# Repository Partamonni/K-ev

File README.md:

# K-ev
K-ev electric motorcycle repo

New, rewritten fork is available at https://github.com/Partamonni/K-ev3

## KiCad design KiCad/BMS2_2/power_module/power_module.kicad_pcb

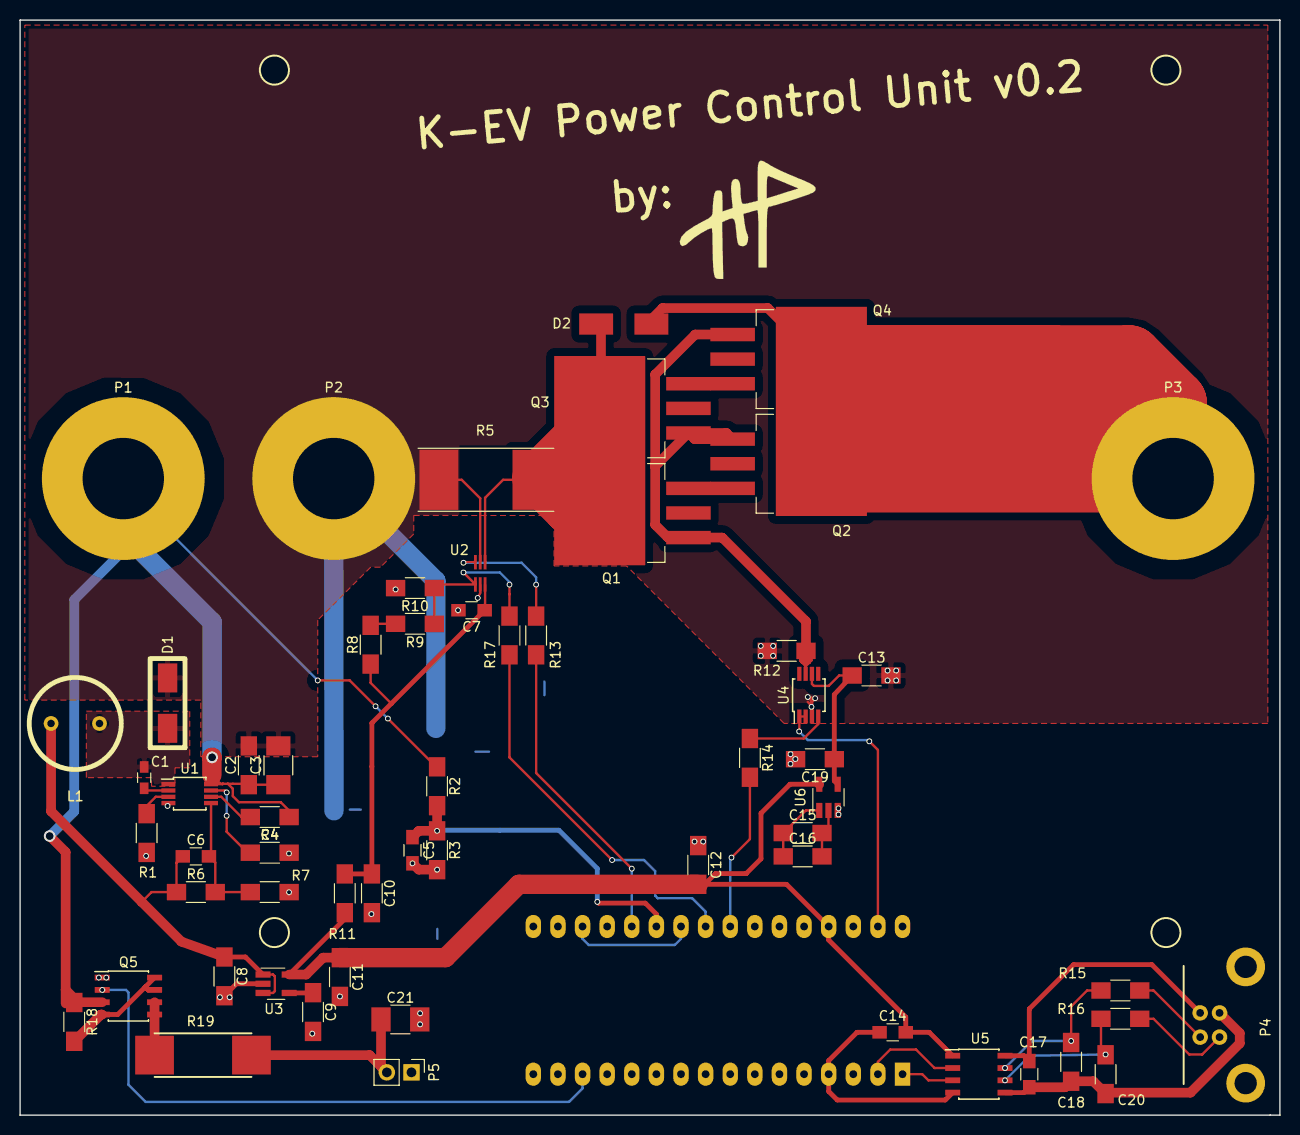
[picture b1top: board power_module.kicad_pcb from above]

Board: 2 copper layers, 130.0 x 113.0 mm, 60 parts (1 on the bottom side), 42 nets.

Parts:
C1: 0.022uF; R_0603_HandSoldering
C2: 0.1uF; R_1206_HandSoldering
C3: 1uF; R_1210_HandSoldering
C4, C8, C10, C11, C12, C13, C15, C16, C18, C20: 1uF; R_1206_HandSoldering
C5, C6, C7, C14, C17: 0.1uF; R_0805_HandSoldering
C9: 1nF; R_1206_HandSoldering
C19: 10uF; R_1206_HandSoldering
C21: 1uF; C_1210_HandSoldering
D1: RFN1L6S; ROHM_RFN1L6S_HAND_SOLDER
D2: TVS; DO-214AA
IC1: ArduinoNano; DIP-32_W15.24mm_Socket_LongPads_Arduino_Nano
L1: 150uH; Bourns_RLB0914-151KL
P1: BATT +; MountingHole_8.4mm_M8_Pad
P2: BATT -; MountingHole_8.4mm_M8_Pad
P3: 72V-; MountingHole_8.4mm_M8_Pad
P4: toRasPi; USB_B_JACK
P5: FAN; Pin_Header_Straight_1x02_Pitch2.54mm
Q1, Q2, Q3, Q4: CSD19535KTT; TO-263-3Lead
Q5: ZXMC10A816N8; SOIC-8_3.9x4.9mm_Pitch1.27mm
R1, R4: 220K; R_1206_HandSoldering
R2: 510K; R_1206_HandSoldering
R3: 27K; R_1206_HandSoldering
R5: 0.2mOhm; Bourns_CSS2H-3920_200uOhm_hand_solder
R6: 1.2K; R_1206_HandSoldering
R7, R13, R14, R17: 1K; R_1206_HandSoldering
R8, R9: 20K; R_1206_HandSoldering
R10, R18: 10K; R_1206_HandSoldering
R11, R15, R16: 100; R_1206_HandSoldering
R12: 100K; R_1206_HandSoldering
R19: 100; TE_SMW_3
U1: LM5009; MSOP-8_3x3mm_Pitch0.65mm
U2: INA214; SC-70-6_Handsoldering
U3: TC1185; SOT-23-5_HandSoldering
U4: LM5112; MSOP-8_3x3mm_Pitch0.65mm
U5: SI8422; SOIC-8_3.9x4.9mm_Pitch1.27mm
U6: MAX1683; SOT-23-5_HandSoldering

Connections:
+5V: C11.1, C12.2, C14.2, IC1.27, R11.2, U3.5, U5.1, U6.4
+5VA: C7.1, C10.1, R8.1, R11.1, U2.3
+10V: C13.1, C19.1, U4.6, U6.2
GND: C2.2, C3.2, C4.2, C5.2, C7.2, C8.2, C9.2, C10.2, C11.2, C12.1, C13.2, C19.2, C21.2, D1.2, IC1.29, P2.1, P5.1, Q5.1, R1.2, R3.2, R5.2, R7.2, R10.2, R12.2, U1.4, U2.2, U2.5, U3.2, U4.1, U4.2, U4.3, U6.1
unnamed: C1.1, D1.1, L1.2, U1.1
unnamed: C1.2, U1.2
unnamed: C2.1, C3.1, P1.1, Q5.3, R2.1, R4.1, R18.1, U1.8
unnamed: C4.1, U1.7
unnamed: C5.1, IC1.20, R2.2, R3.1
unnamed: C6.1, C8.1, L1.1, R6.1, U3.1, U3.3
unnamed: C6.2, R6.2, R7.1, U1.5
unnamed: C9.1, U3.4
unnamed: C14.1, IC1.4, U5.4
unnamed: C15.1, C16.1, U6.5
unnamed: C15.2, C16.2, U6.3
unnamed: C17.1, C18.2, C20.2, P4.4, U5.5
unnamed: C17.2, P4.1, U5.8
unnamed: C18.1, R15.1, U5.7
unnamed: C20.1, R16.2, U5.6
unnamed: C21.1, P5.2, R19.1
unnamed: D2.1, Q1.2, Q3.2, R5.1, U2.4
unnamed: D2.2, P3.1, Q2.2, Q4.2
unnamed: IC1.1, U5.3
unnamed: IC1.2, U5.2
unnamed: IC1.14, Q5.2
unnamed: IC1.17, IC1.21
unnamed: IC1.19, R13.2
unnamed: IC1.22, R17.2
unnamed: IC1.23, R14.2
unnamed: P4.2, R15.2
unnamed: P4.3, R16.1
unnamed: Q1.1, Q2.1, Q3.1, Q4.1, R12.1, U4.7
unnamed: Q1.3, Q2.3
unnamed: Q3.3, Q4.3
unnamed: Q5.4, Q5.7, Q5.8, R18.2
unnamed: Q5.5, Q5.6, R19.2
unnamed: R1.1, U1.3
unnamed: R4.2, U1.6
unnamed: R8.2, R9.1
unnamed: R9.2, R10.1, R17.1, U2.1
unnamed: R13.1, U2.6
unnamed: R14.1, U4.4

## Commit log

2017-09-28 Poured a bit of my soul there
    Monni
2017-09-28 First migration to git
2017-09-28 test2
2017-09-28 Revert "test2"
    This reverts commit 11873fafb9620dfb3f41b3c2ff70722c8dd9cfc9.
2017-09-28 Testing
2017-09-28 testi3
2017-10-02 Schematics uploads for power control unit
2017-10-03 Arduino code upload
    Also added one junction in schemas
2017-10-04 Third day coding
    Now bare functional
2017-10-05 Added direct pin manipulation
    Also, STrated
2017-10-05 Slight fuck up with this git
2017-10-05 Revert "Slight fuck up with this git"
    This reverts commit c466bf0ab85ec2846da82903cb7f0dc0e604bdf4.
2017-10-05 Slight adjust to code
2017-10-09 Continuing development
    Watchdog, commenting, host-given shut command, host availability confirming,
2017-10-09 Added option for host to respond and recontinue program
    Also, modified loops which use DEBUG flag, few '<' marks changed to '>' marks
2017-10-09 Divided critical failures
2017-10-17 oh uh
    For arduino: MAX31820 temperature monitoring
    For Raspberry: lgpl entry
2017-10-17 Temperature readings
    Continued work with the implement
2017-10-18 sumthing
    I fill this later
2017-10-22 Lots of stuff
    - #Defines didn't work, back to const int
    - Onewire declaration must be global
    - Wrote tempAdr table
    - deleted two unused variables and added criticalTFailure
    - changed all bitwise operations to neater forms
    - added a trap for setup cycle if ds.reset finds failure on com-line
2017-10-24 First working version
    - Added configuring script and modified head comment accordingly
    - Changed DEBUG back to to #define -version, also added VERBOSE tag along with DEBUG
    - Address table formatted with full zeroes
    - wdt_disable() added to prevent still occurred wdt reset loop
    - Added a lot of debug code to be outputted to serial
    - Adress validity check fixed, checks crc byte now
2017-10-24 Slight adjustments
2017-11-07 asd
    asd
2017-11-20 Revert "Slight adjustments"
    This reverts commit 7b9bba6fb82006954818c30b39243f595e4735de.
2017-12-01 Revert "asd"
    This reverts commit 4e9a0a506c0f58515d602d51b063e07c4e7a7c9e.
2017-12-22 Trying to get this mf to work
    ya know how desperate I am
2018-01-26 Status quo = stripped of serial stuff
2018-02-07 Amperage has some serial work to do
    Working, continued to implement some serial analyzing.
    (Note to self: parent pointer doesn't work in class functions, must create m_parent pointer within class to access parent within class functions.)
2018-02-07 Now controlled input from serial
2018-02-09 Fixed motion bug, all destinations are noww hard coded
2018-02-09 Added Celsius signs to new incoming values
2018-02-25 It works, maybe?
2018-09-05 Now that's a tangled mess
2018-09-07 Defined functions I want to implement to the menu
2018-09-11 Kicad and button pin change
2018-09-11 delay
2018-09-11 trigger
2018-09-11 Revert "delay"
    This reverts commit 2a76ca7d03e3e0bc33578b970b199577c49e2c8e.
2018-09-11 tidying bubblegums
2018-09-11 gitignore
2018-09-11 Revert "trigger"
    This reverts commit 1e6bff870b3f3ccacaf5de3ed2d35f567c77fe88.
2018-09-12 Trying something
2018-09-12 Simplifying code to see if it fixes anything
2018-10-16 Added splash notifications
    - Animations done
    - Works
2018-10-22 kicad + arduino
2018-10-29 Added clock for upper right corner
2018-11-02 Added slides for all entries
    All entries are now derived from Entry -class
2018-11-03 Fine tuning entry mechanisms
    Now repeated entry toggles doesn't leave entry open when dropdown->entryOpen != true, also motor toggles doesn't slide previous entry away.
2018-11-03 Update Arduino code/Power_module1_3/Power_module1_3.ino
    Started soc work, simplified current and voltage calculations. (Current calculation was even wrong before this)
2018-11-20 Power module improved, KiCad updates
2018-11-20 Uh, changes?
2018-11-20 Error log added
2018-11-22 DOUBLE LENGTH WAS WROOOOOOONG!
2018-11-27 wut?
2018-12-05 Serial log now nice and functional
    Also splashes now are nice
